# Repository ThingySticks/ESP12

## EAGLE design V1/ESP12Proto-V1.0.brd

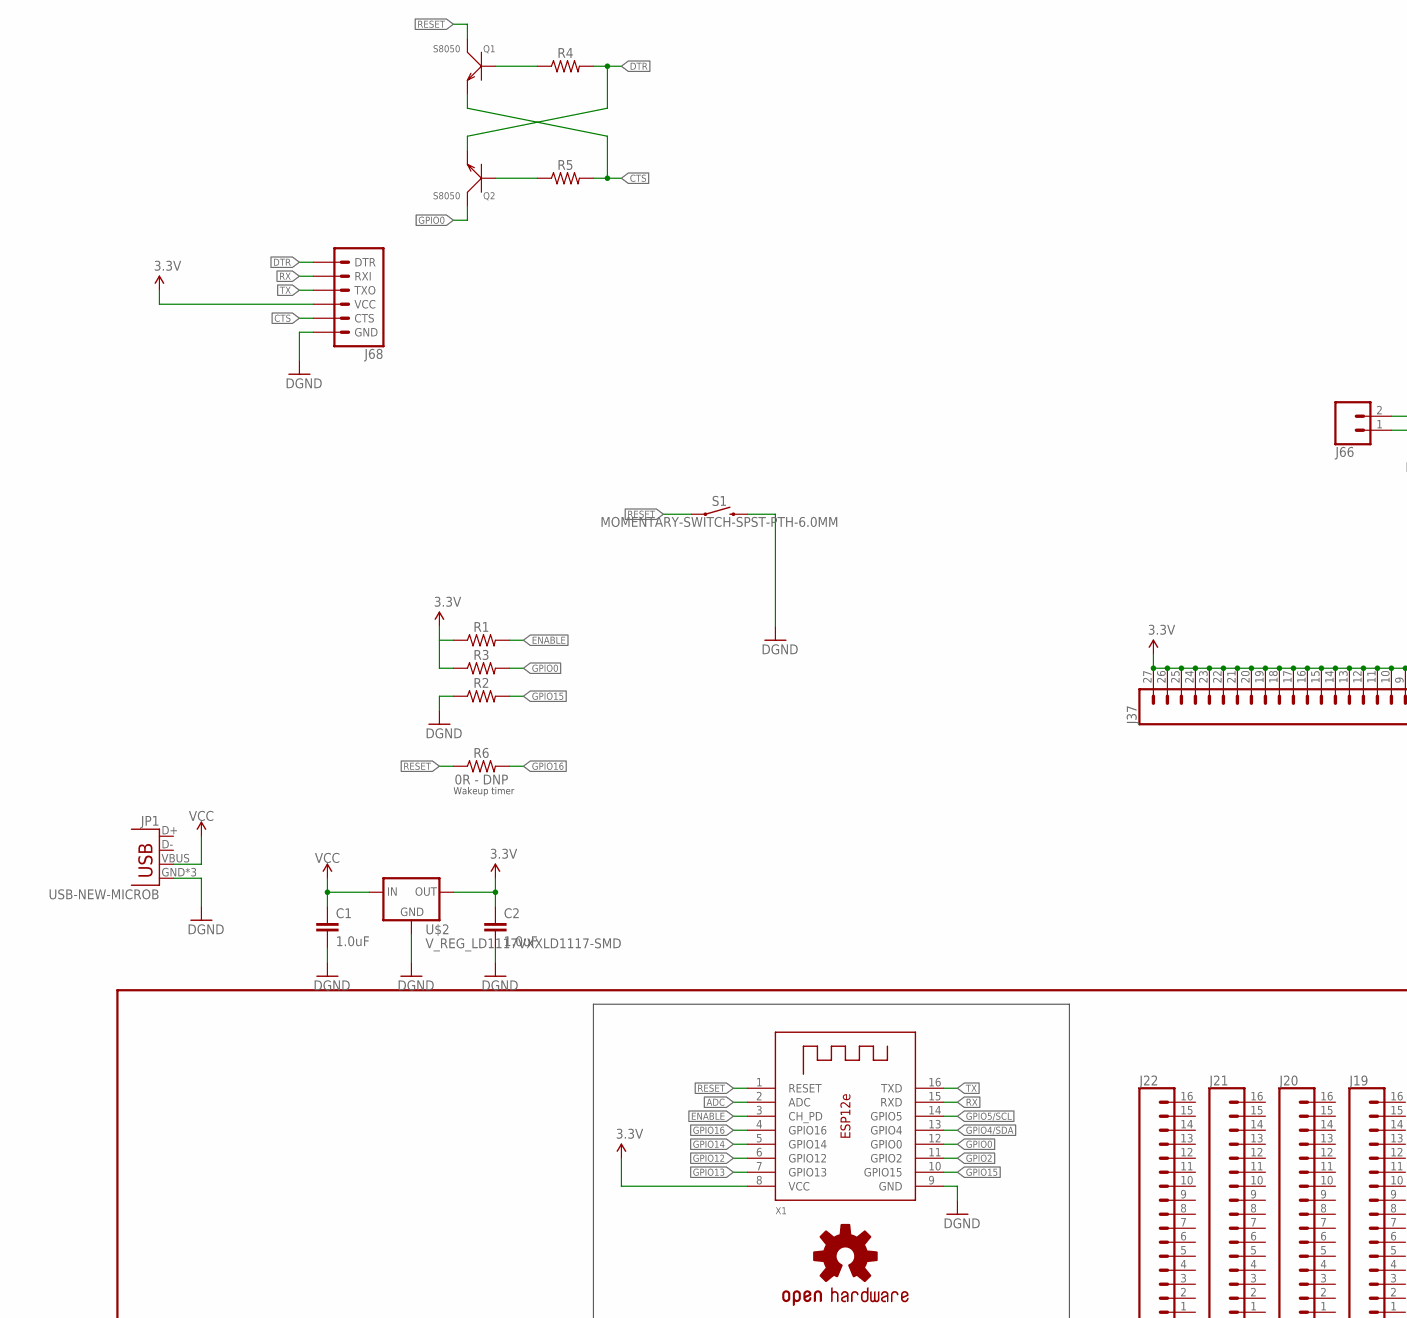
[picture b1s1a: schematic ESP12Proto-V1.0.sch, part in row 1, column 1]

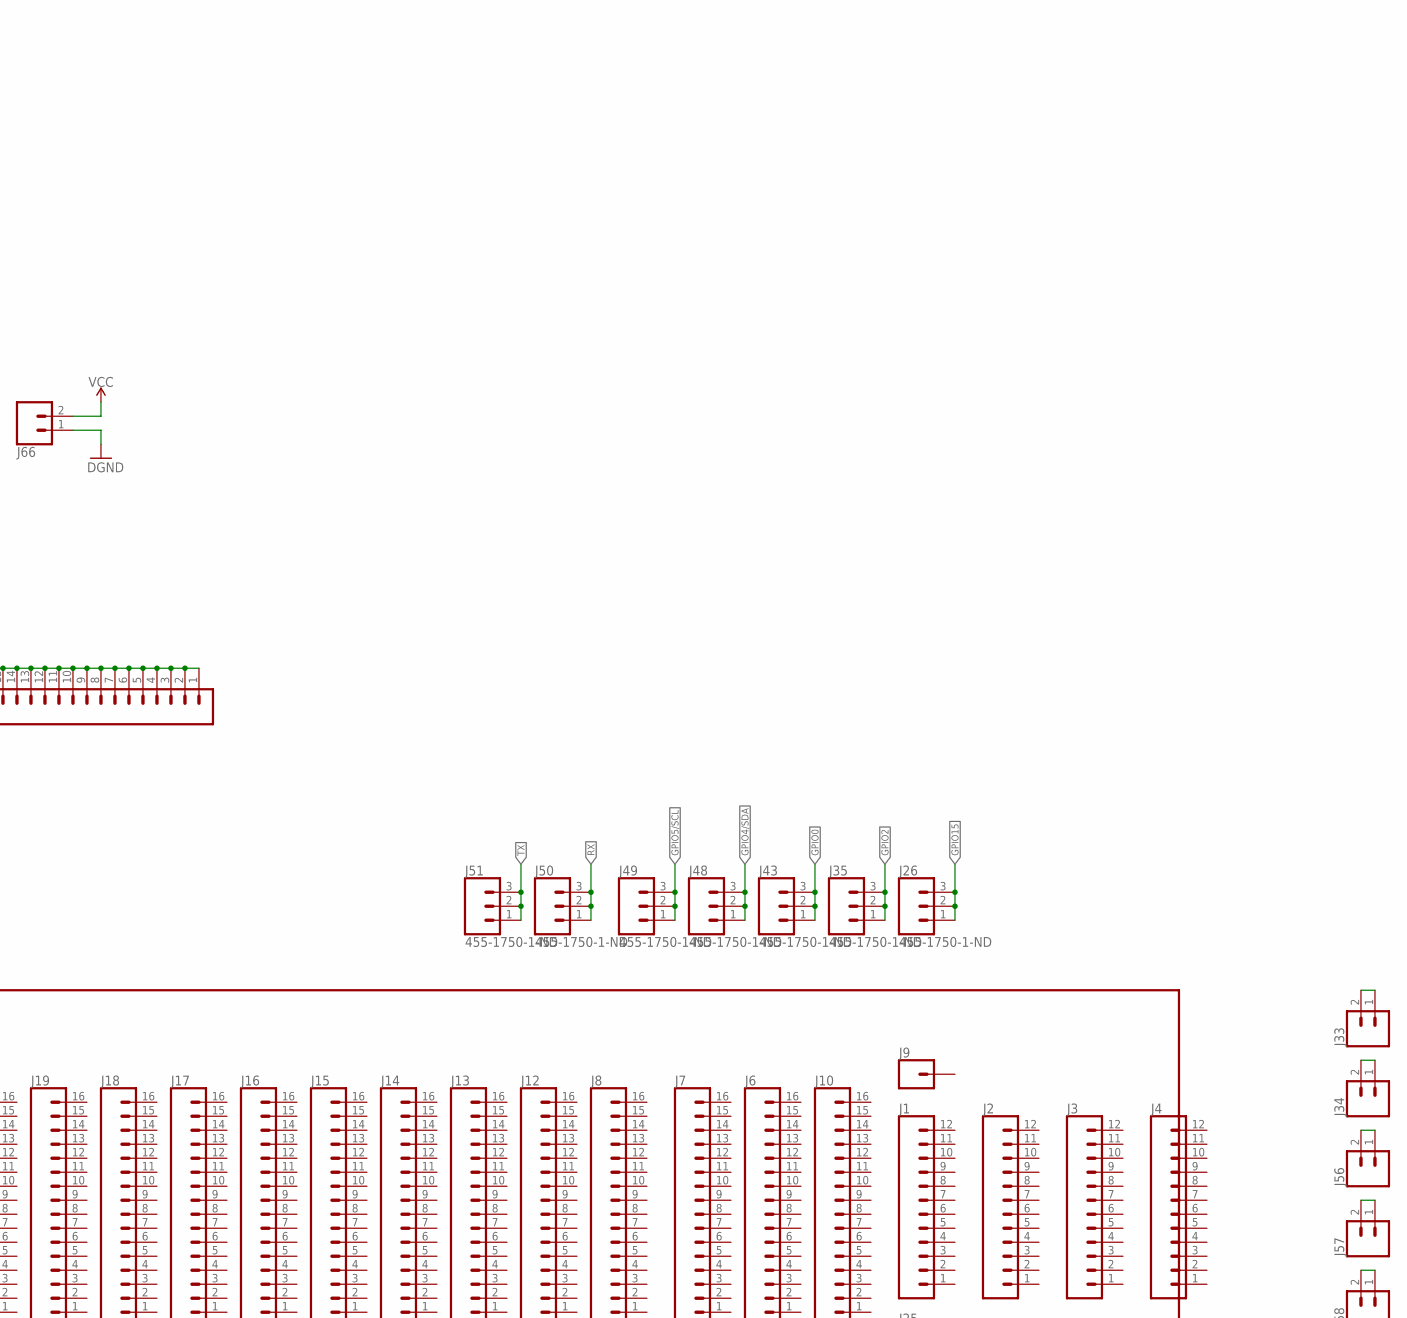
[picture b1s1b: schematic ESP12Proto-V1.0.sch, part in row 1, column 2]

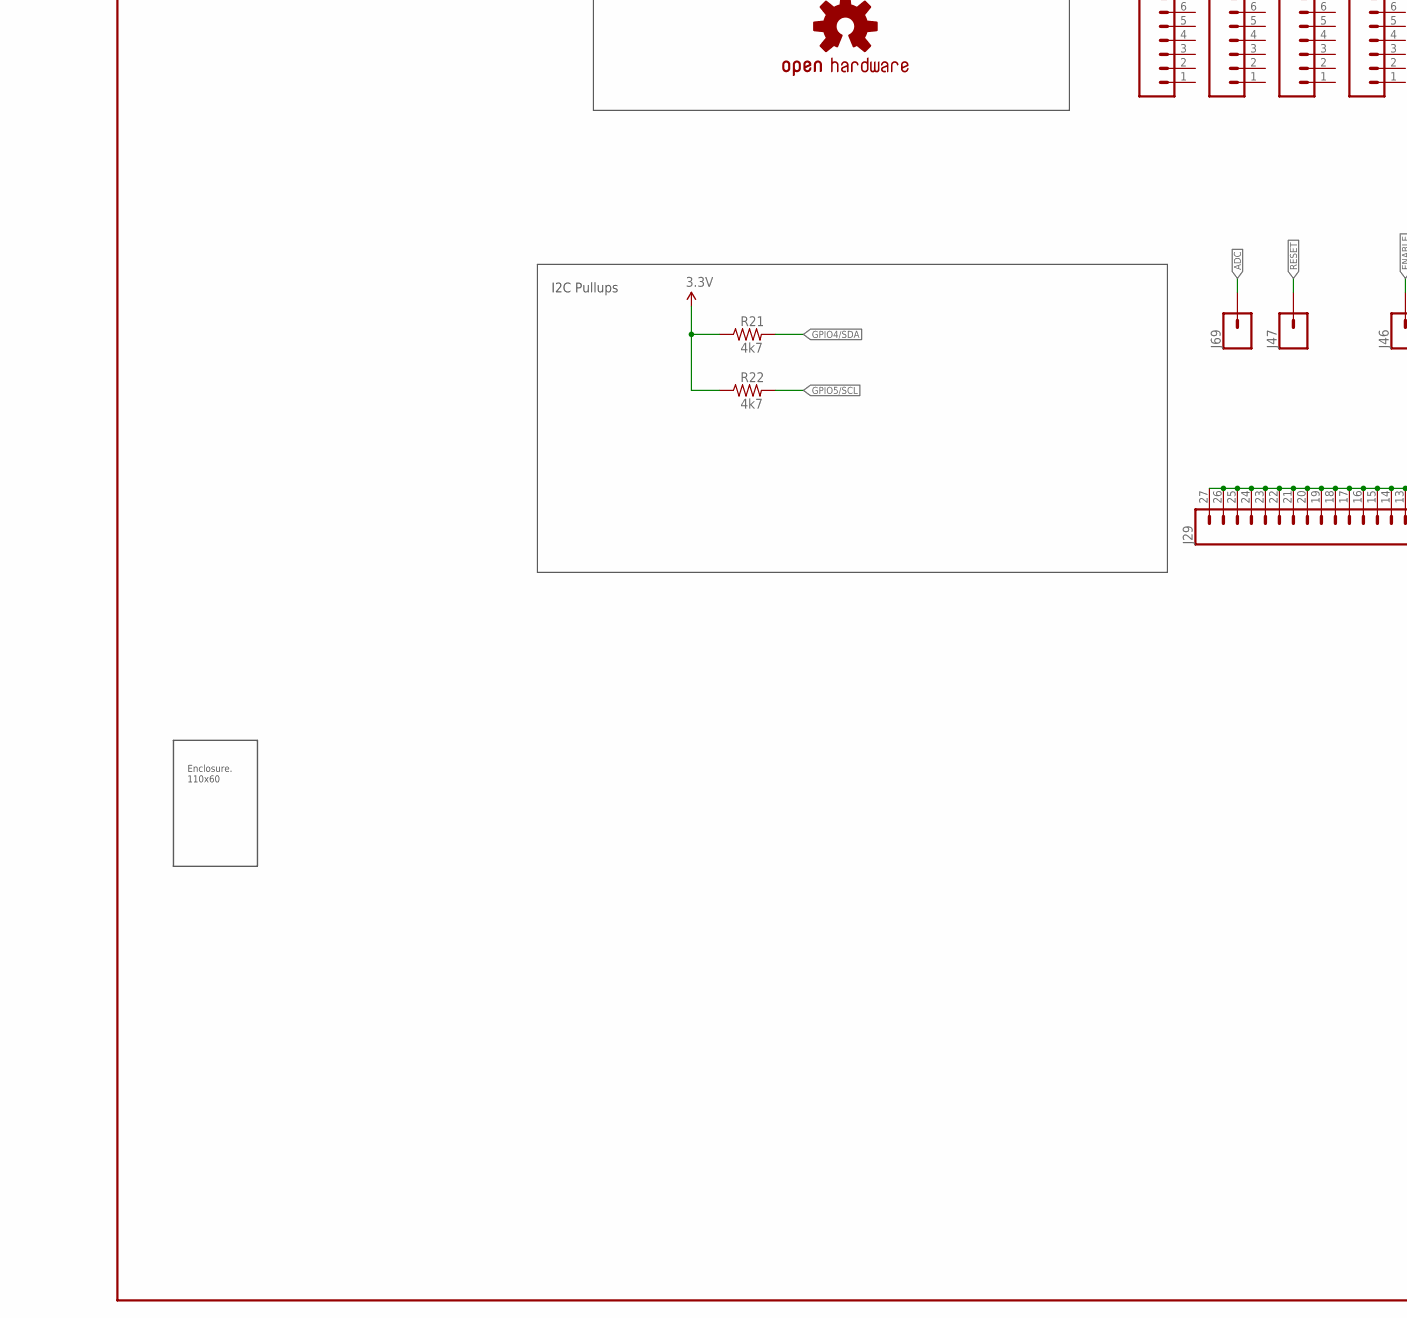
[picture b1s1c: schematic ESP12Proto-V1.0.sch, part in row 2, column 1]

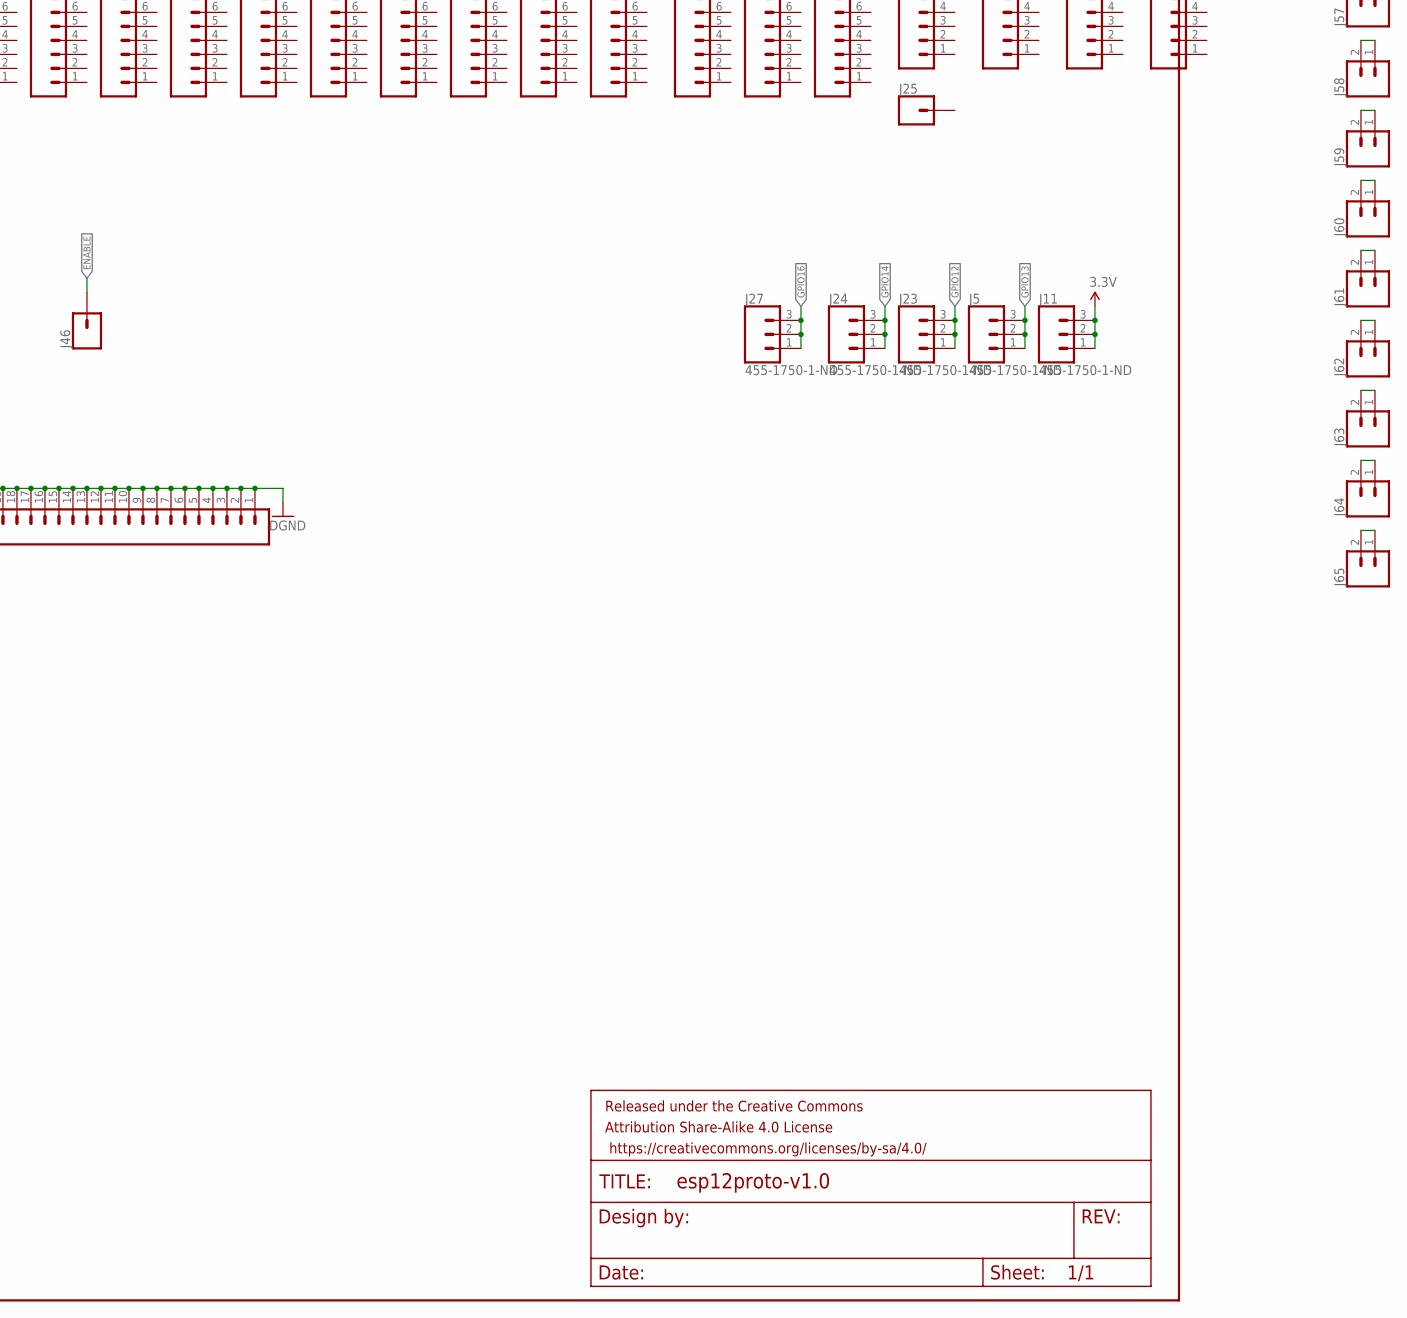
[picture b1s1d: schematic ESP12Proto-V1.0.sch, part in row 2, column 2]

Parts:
C1, C2: 1.0uF; 0805
FRAME2: FRAME-LEDGER; CREATIVE_COMMONS
J1, J2, J3, J4: CONN_12NO_SILK; 1X12_NO_SILK
J5, J11, J23, J24, J26, J27, J35, J43, J48, J49, J50, J51: 455-1750-1-ND; 1X03
J6, J7, J8, J10, J12, J13, J14, J15, J16, J17, J18, J19, J20, J21, J22: CONN_161X16_NO_SILK; 1X16_NO_SILK
J9, J25, J46, J47, J69: CONN_01PTH_NO_SILK_YES_STOP; 1X01_NO_SILK
J29, J37: CONN_27; 1X27
J33, J34, J56, J57, J58, J59, J60, J61, J62, J63, J64, J65: CONN_02; 1X02
J66: CONN_02-JST-2MM-SMT; JST-2-SMD
J68: 6_PIN_SERIAL_TARGETSILK; 6_PIN_SERIAL_TARGET_SIDE_W_SILK
JP1: USB-NEW-MICROB; USB-MICROB
LOGO1: OSHW-LOGOM; OSHW-LOGO-M
Q1, Q2: S8050; SOT-23
R1, R2, R3, R4, R5: 0805
R6: 0R - DNP; 0805
R21, R22: 4k7; 0805
S1: MOMENTARY-SWITCH-SPST-PTH-6.0MM; TACTILE_SWITCH_PTH_6.0MM
U$1: CAMDENBOSS-ENCLOSURE-110X60BOTH-EXTENDED-WIDE; CAMDENBOSS_ENCLOSURE_110X60_WIDE_EXTENDED
U$2: V_REG_LD1117VXXLD1117-SMD; SOT223
X1: ESP-12E

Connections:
3.3V: C2.1, J11.1, J11.2, J11.3, J37.1, J37.2, J37.3, J37.4, J37.5, J37.6, J37.7, J37.8, J37.9, J37.10, J37.11, J37.12, J37.13, J37.14, J37.15, J37.16, J37.17, J37.18, J37.19, J37.20, J37.21, J37.22, J37.23, J37.24, J37.25, J37.26, J37.27, J68.P$4 (VCC), R1.1, R3.1, R21.1, R22.1, U$2.2 (OUT), X1.8 (VCC)
ADC: J69.1, X1.2 (ADC)
CTS: J68.P$5 (CTS), Q1.2 (E), R5.2
DTR: J68.P$1 (DTR), Q2.2 (E), R4.2
ENABLE: J46.1, R1.2, X1.3 (CH_PD)
GND: C1.2, C2.2, J29.1, J29.2, J29.3, J29.4, J29.5, J29.6, J29.7, J29.8, J29.9, J29.10, J29.11, J29.12, J29.13, J29.14, J29.15, J29.16, J29.17, J29.18, J29.19, J29.20, J29.21, J29.22, J29.23, J29.24, J29.25, J29.26, J29.27, J66.1 (2), J68.P$6 (GND), JP1.GND, JP1.MT1 (GND), JP1.MT2 (GND), R2.1, S1.3 (2), U$2.1 (GND), X1.9 (GND)
GPIO0: J43.1, J43.2, J43.3, Q2.3 (C), R3.2, X1.12 (GPIO0)
GPIO2: J35.1, J35.2, J35.3, X1.11 (GPIO2)
GPIO4/SDA: J48.1, J48.2, J48.3, R21.2, X1.13 (GPIO4)
GPIO5/SCL: J49.1, J49.2, J49.3, R22.2, X1.14 (GPIO5)
GPIO12: J23.1, J23.2, J23.3, X1.6 (GPIO12)
GPIO13: J5.1, J5.2, J5.3, X1.7 (GPIO13)
GPIO14: J24.1, J24.2, J24.3, X1.5 (GPIO14)
GPIO15: J26.1, J26.2, J26.3, R2.2, X1.10 (GPIO15)
GPIO16: J27.1, J27.2, J27.3, R6.2, X1.4 (GPIO16)
unnamed: J65.1, J65.2
unnamed: J64.1, J64.2
unnamed: J63.1, J63.2
unnamed: J62.1, J62.2
unnamed: J61.1, J61.2
unnamed: J60.1, J60.2
unnamed: J59.1, J59.2
unnamed: J58.1, J58.2
unnamed: J57.1, J57.2
unnamed: J56.1, J56.2
unnamed: J34.1, J34.2
unnamed: J33.1, J33.2
unnamed: Q2.1 (B), R5.1
unnamed: Q1.1 (B), R4.1
RESET: J47.1, Q1.3 (C), R6.1, S1.1, X1.1 (RESET)
RX: J50.1, J50.2, J50.3, J68.P$3 (RXI), X1.15 (RXD)
TX: J51.1, J51.2, J51.3, J68.P$2 (TXO), X1.16 (TXD)
VCC: C1.1, J66.2 (1), JP1.VBUS, U$2.3 (IN)

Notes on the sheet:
I2C Pullups
Wakeup timer

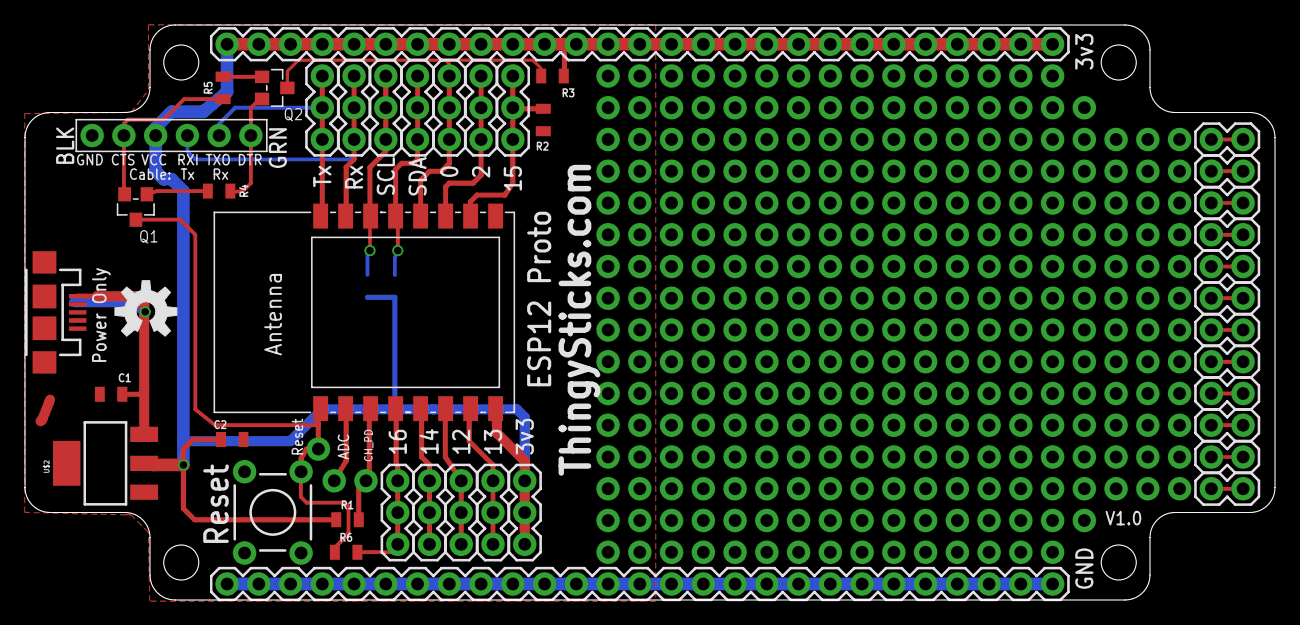
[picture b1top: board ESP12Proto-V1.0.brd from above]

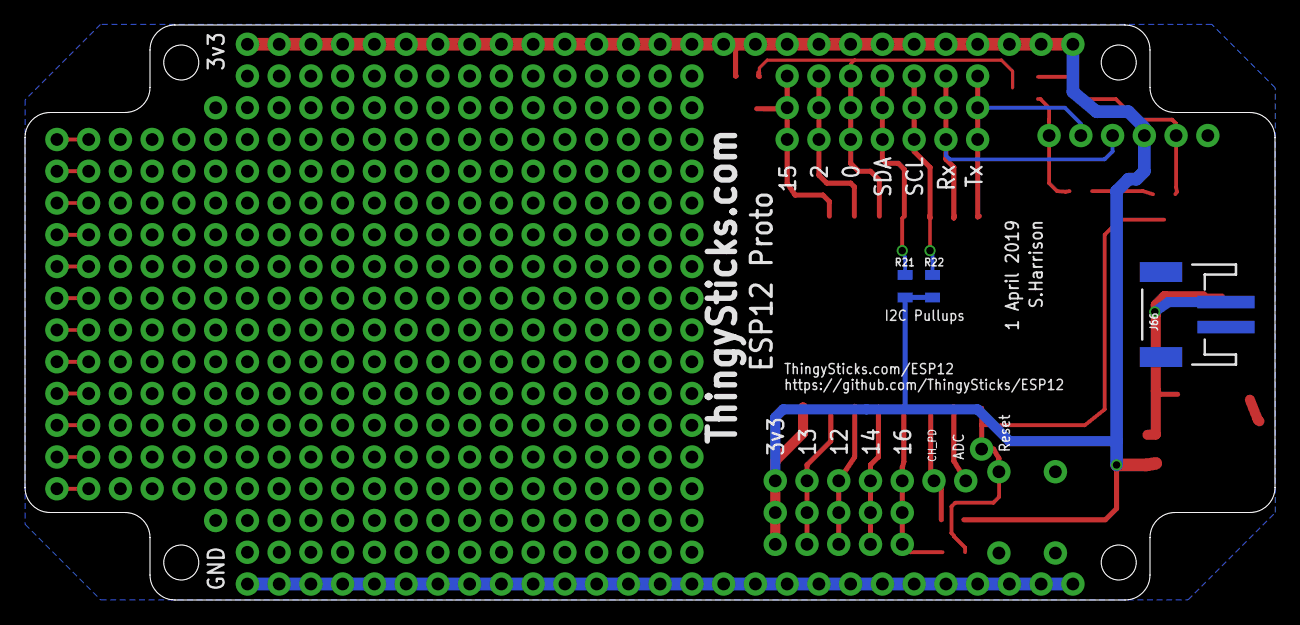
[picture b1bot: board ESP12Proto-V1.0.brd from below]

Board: 2 copper layers, 100.0 x 46.0 mm, 71 parts (3 on the bottom side), 33 nets.

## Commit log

2019-04-03 Initial version

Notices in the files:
parts and their libraries:
SparkFun-Aesthetics: Licensing: Creative Commons ShareAlike 4.0 International - https://creativecommons.org/licenses/by-sa/4.0
SparkFun-Aesthetics: Released under the Creative Commons Attribution Share-Alike 4.0 License
SparkFun-Aesthetics: https://creativecommons.org/licenses/by-sa/4.0
